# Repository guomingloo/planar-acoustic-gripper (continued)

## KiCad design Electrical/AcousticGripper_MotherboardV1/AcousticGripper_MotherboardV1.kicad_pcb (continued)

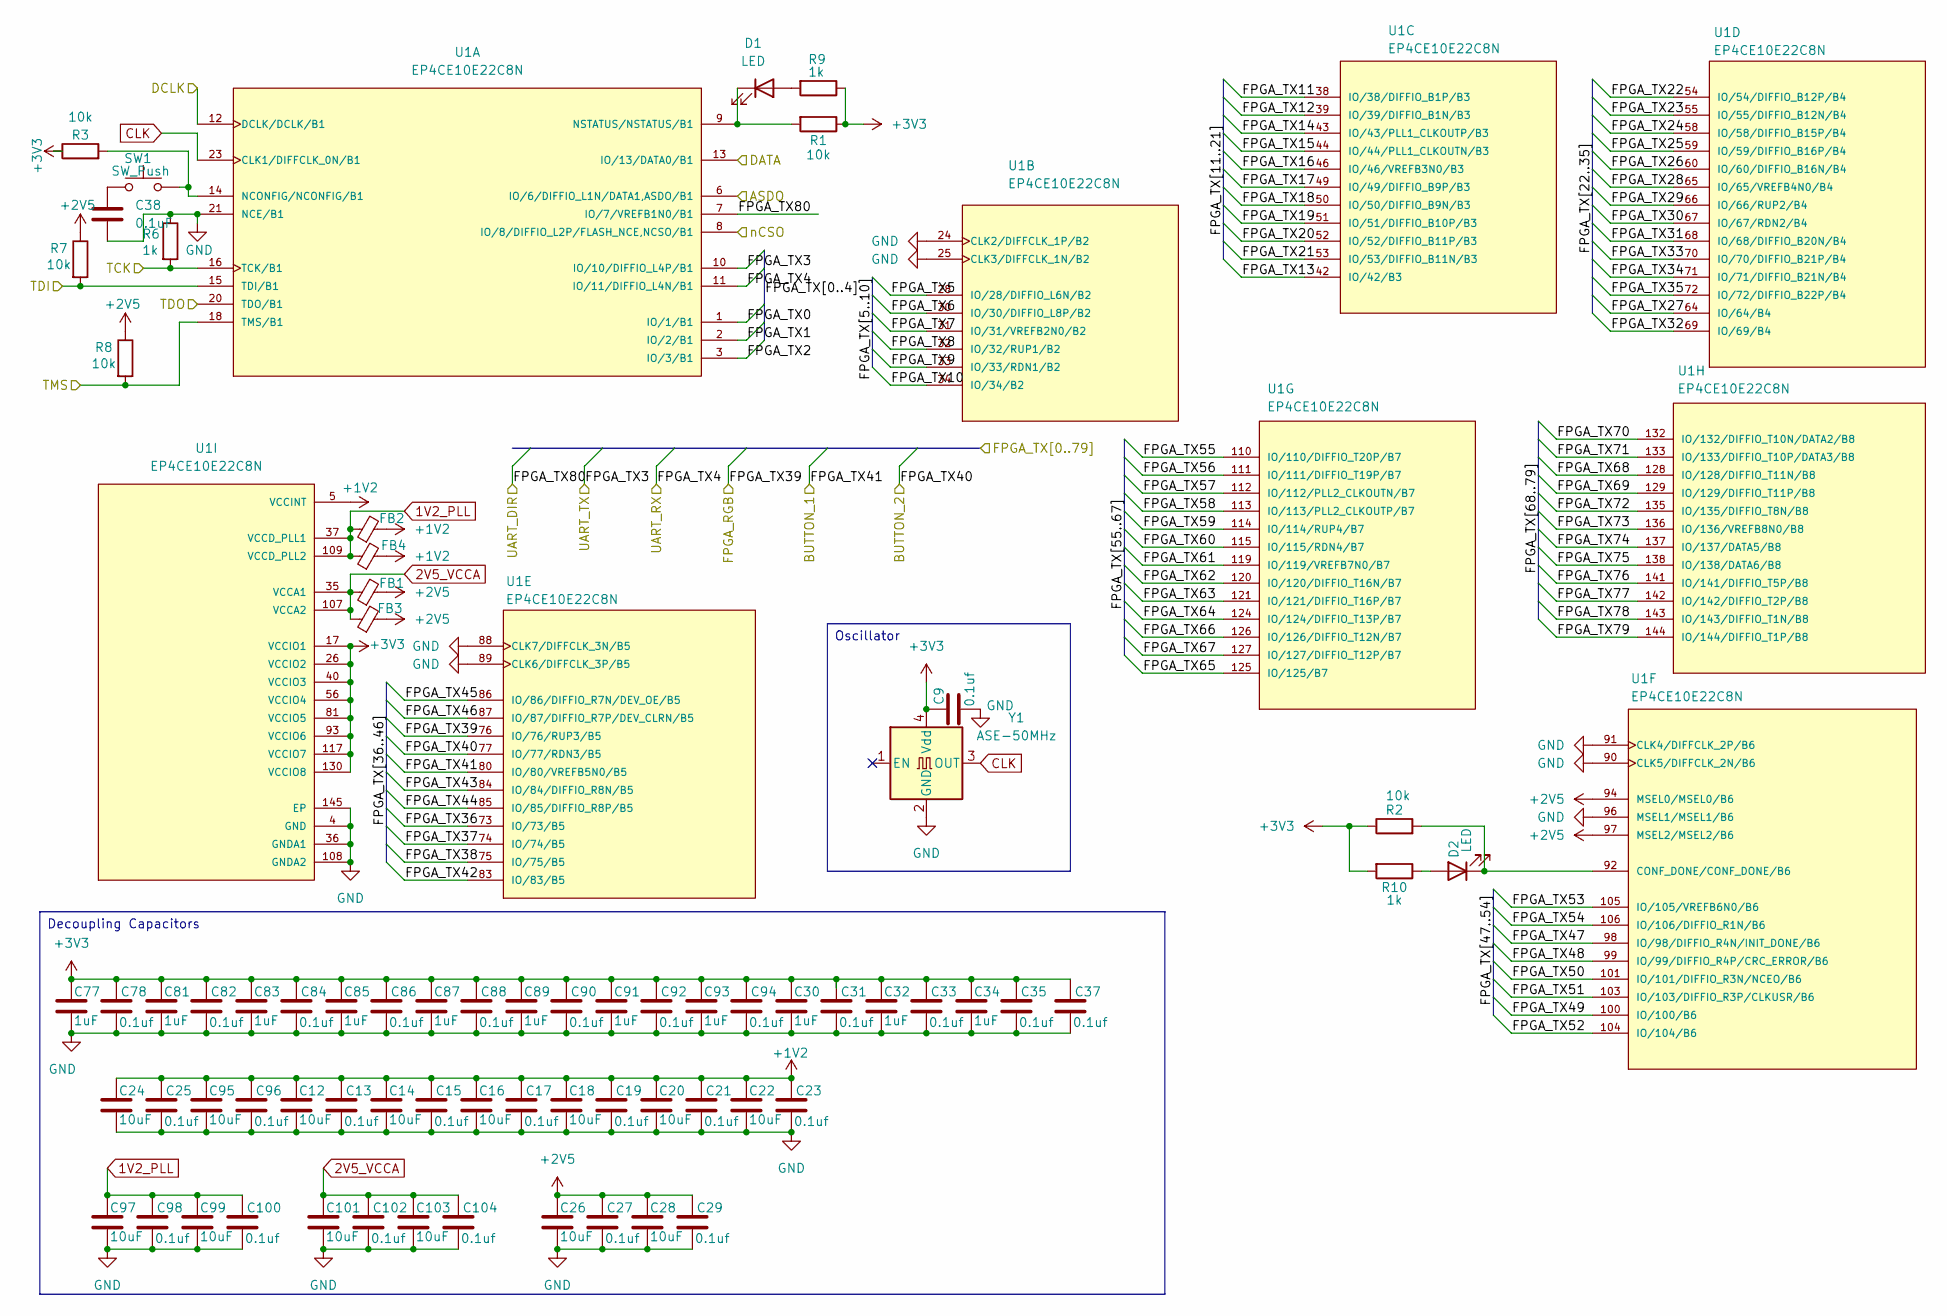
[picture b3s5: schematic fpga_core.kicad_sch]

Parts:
C9, C13, C15, C17, C19, C21, C23, C25, C27, C29, C31, C33, C35, C37, C78, C82, C84, C86, C88, C90, C92, C94, C96, C98, C100, C102, C104: 0.1uf; C_0402_1005Metric
C12, C14, C16, C18, C20, C22, C24, C26, C28, C95, C97, C99, C101, C103: 10uF; C_0402_1005Metric
C30, C32, C34, C77, C81, C83, C85, C87, C89, C91, C93: 1uF; C_0402_1005Metric
C38: 0.1uF; C_0402_1005Metric
D1, D2: LED; LED_D3.0mm
FB1, FB2, FB3, FB4: FerriteBead_Small; L_0402_1005Metric
R1, R2, R3, R7, R8: 10k; R_0402_1005Metric
R6, R9, R10: 1k; R_0402_1005Metric
SW1: SW_Push; SW_Push_SPST_NO_Alps_SKRK
U1: EP4CE10E22C8N; QFP50P2200X2200X165-145N
Y1: ASE-50MHz; Oscillator_SMD_Abracon_ASE-4Pin_3.2x2.5mm

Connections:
1V2_PLL: C97.1, C98.1, C99.1, C100.1, FB2.1, FB4.1, U1.37 (VCCD_PLL1), U1.109 (VCCD_PLL2)
2V5_VCCA: C101.1, C102.1, C103.1, C104.1, FB1.1, FB3.1, U1.35 (VCCA1), U1.107 (VCCA2)
+1V2: C12.1, C13.1, C14.1, C15.1, C16.1, C17.1, C18.1, C19.1, C20.1, C21.1, C22.1, C23.1, C24.1, C25.1, C95.1, C96.1, FB2.2, FB4.2, U1.5 (VCCINT), U1.29 (VCCINT), U1.45 (VCCINT), U1.61 (VCCINT), U1.78 (VCCINT), U1.102 (VCCINT), U1.116 (VCCINT), U1.134 (VCCINT); also elsewhere on the board
+2V5: C26.1, C27.1, C28.1, C29.1, FB1.2, FB3.2, R7.1, R8.1, U1.94 (MSEL0/MSEL0/B6), U1.97 (MSEL2/MSEL2/B6); also elsewhere on the board
+3V3: C9.1, C30.1, C31.1, C32.1, C33.1, C34.1, C35.1, C37.1, C77.1, C78.1, C81.1, C82.1, C83.1, C84.1, C85.1, C86.1, C87.1, C88.1, C89.1, C90.1, C91.1, C92.1, C93.1, C94.1, R1.1, R2.1, R3.1, R9.1, R10.2, U1.17 (VCCIO1), U1.26 (VCCIO2), U1.40 (VCCIO3), U1.47 (VCCIO3), U1.56 (VCCIO4), U1.62 (VCCIO4), U1.81 (VCCIO5), U1.93 (VCCIO6), U1.117 (VCCIO7), U1.122 (VCCIO7), U1.130 (VCCIO8), U1.139 (VCCIO8), Y1.4 (Vdd); also elsewhere on the board
/Configuration/ASDO: U1.6 (IO/6/DIFFIO_L1N/DATA1,ASDO/B1); also elsewhere on the board
/Configuration/DATA: U1.13 (IO/13/DATA0/B1); also elsewhere on the board
/Configuration/DCLK: U1.12 (DCLK/DCLK/B1); also elsewhere on the board
/Configuration/TCK: R6.2, U1.16 (TCK/B1); also elsewhere on the board
/Configuration/TDI: R7.2, U1.15 (TDI/B1); also elsewhere on the board
/Configuration/TDO: U1.20 (TDO/B1); also elsewhere on the board
/Configuration/TMS: R8.2, U1.18 (TMS/B1); also elsewhere on the board
/Configuration/nCSO: U1.8 (IO/8/DIFFIO_L2P/FLASH_NCE,NCSO/B1); also elsewhere on the board
/FPGA_Core/FPGA_TX0: U1.1 (IO/1/B1); also elsewhere on the board
/FPGA_Core/FPGA_TX1: U1.2 (IO/2/B1); also elsewhere on the board
/FPGA_Core/FPGA_TX2: U1.3 (IO/3/B1); also elsewhere on the board
/FPGA_Core/FPGA_TX3: U1.10 (IO/10/DIFFIO_L4P/B1); also elsewhere on the board
/FPGA_Core/FPGA_TX4: U1.11 (IO/11/DIFFIO_L4N/B1); also elsewhere on the board
/FPGA_Core/FPGA_TX5: U1.28 (IO/28/DIFFIO_L6N/B2); also elsewhere on the board
/FPGA_Core/FPGA_TX6: U1.30 (IO/30/DIFFIO_L8P/B2); also elsewhere on the board
/FPGA_Core/FPGA_TX7: U1.31 (IO/31/VREFB2N0/B2); also elsewhere on the board
/FPGA_Core/FPGA_TX8: U1.32 (IO/32/RUP1/B2); also elsewhere on the board
/FPGA_Core/FPGA_TX9: U1.33 (IO/33/RDN1/B2); also elsewhere on the board
/FPGA_Core/FPGA_TX10: U1.34 (IO/34/B2); also elsewhere on the board
/FPGA_Core/FPGA_TX11: U1.38 (IO/38/DIFFIO_B1P/B3); also elsewhere on the board
/FPGA_Core/FPGA_TX12: U1.39 (IO/39/DIFFIO_B1N/B3); also elsewhere on the board
/FPGA_Core/FPGA_TX13: U1.42 (IO/42/B3); also elsewhere on the board
/FPGA_Core/FPGA_TX14: U1.43 (IO/43/PLL1_CLKOUTP/B3); also elsewhere on the board
/FPGA_Core/FPGA_TX15: U1.44 (IO/44/PLL1_CLKOUTN/B3); also elsewhere on the board
/FPGA_Core/FPGA_TX16: U1.46 (IO/46/VREFB3N0/B3); also elsewhere on the board
/FPGA_Core/FPGA_TX17: U1.49 (IO/49/DIFFIO_B9P/B3); also elsewhere on the board
/FPGA_Core/FPGA_TX18: U1.50 (IO/50/DIFFIO_B9N/B3); also elsewhere on the board
/FPGA_Core/FPGA_TX19: U1.51 (IO/51/DIFFIO_B10P/B3); also elsewhere on the board
/FPGA_Core/FPGA_TX20: U1.52 (IO/52/DIFFIO_B11P/B3); also elsewhere on the board
/FPGA_Core/FPGA_TX21: U1.53 (IO/53/DIFFIO_B11N/B3); also elsewhere on the board
/FPGA_Core/FPGA_TX22: U1.54 (IO/54/DIFFIO_B12P/B4); also elsewhere on the board
/FPGA_Core/FPGA_TX23: U1.55 (IO/55/DIFFIO_B12N/B4); also elsewhere on the board
/FPGA_Core/FPGA_TX24: U1.58 (IO/58/DIFFIO_B15P/B4); also elsewhere on the board
/FPGA_Core/FPGA_TX25: U1.59 (IO/59/DIFFIO_B16P/B4); also elsewhere on the board
/FPGA_Core/FPGA_TX26: U1.60 (IO/60/DIFFIO_B16N/B4); also elsewhere on the board
/FPGA_Core/FPGA_TX27: U1.64 (IO/64/B4); also elsewhere on the board
/FPGA_Core/FPGA_TX28: U1.65 (IO/65/VREFB4N0/B4); also elsewhere on the board
/FPGA_Core/FPGA_TX29: U1.66 (IO/66/RUP2/B4); also elsewhere on the board
/FPGA_Core/FPGA_TX30: U1.67 (IO/67/RDN2/B4); also elsewhere on the board
/FPGA_Core/FPGA_TX31: U1.68 (IO/68/DIFFIO_B20N/B4); also elsewhere on the board
/FPGA_Core/FPGA_TX32: U1.69 (IO/69/B4); also elsewhere on the board
/FPGA_Core/FPGA_TX33: U1.70 (IO/70/DIFFIO_B21P/B4); also elsewhere on the board
/FPGA_Core/FPGA_TX34: U1.71 (IO/71/DIFFIO_B21N/B4); also elsewhere on the board
/FPGA_Core/FPGA_TX35: U1.72 (IO/72/DIFFIO_B22P/B4); also elsewhere on the board
/FPGA_Core/FPGA_TX36: U1.73 (IO/73/B5); also elsewhere on the board
/FPGA_Core/FPGA_TX37: U1.74 (IO/74/B5); also elsewhere on the board
/FPGA_Core/FPGA_TX38: U1.75 (IO/75/B5); also elsewhere on the board
/FPGA_Core/FPGA_TX39: U1.76 (IO/76/RUP3/B5); also elsewhere on the board
/FPGA_Core/FPGA_TX40: U1.77 (IO/77/RDN3/B5); also elsewhere on the board
/FPGA_Core/FPGA_TX41: U1.80 (IO/80/VREFB5N0/B5); also elsewhere on the board
/FPGA_Core/FPGA_TX42: U1.83 (IO/83/B5); also elsewhere on the board
/FPGA_Core/FPGA_TX43: U1.84 (IO/84/DIFFIO_R8N/B5); also elsewhere on the board
/FPGA_Core/FPGA_TX44: U1.85 (IO/85/DIFFIO_R8P/B5); also elsewhere on the board
/FPGA_Core/FPGA_TX45: U1.86 (IO/86/DIFFIO_R7N/DEV_OE/B5); also elsewhere on the board
/FPGA_Core/FPGA_TX46: U1.87 (IO/87/DIFFIO_R7P/DEV_CLRN/B5); also elsewhere on the board
/FPGA_Core/FPGA_TX47: U1.98 (IO/98/DIFFIO_R4N/INIT_DONE/B6); also elsewhere on the board
/FPGA_Core/FPGA_TX48: U1.99 (IO/99/DIFFIO_R4P/CRC_ERROR/B6); also elsewhere on the board
/FPGA_Core/FPGA_TX49: U1.100 (IO/100/B6); also elsewhere on the board
/FPGA_Core/FPGA_TX50: U1.101 (IO/101/DIFFIO_R3N/NCEO/B6); also elsewhere on the board
/FPGA_Core/FPGA_TX51: U1.103 (IO/103/DIFFIO_R3P/CLKUSR/B6); also elsewhere on the board
/FPGA_Core/FPGA_TX52: U1.104 (IO/104/B6); also elsewhere on the board
/FPGA_Core/FPGA_TX53: U1.105 (IO/105/VREFB6N0/B6); also elsewhere on the board
/FPGA_Core/FPGA_TX54: U1.106 (IO/106/DIFFIO_R1N/B6); also elsewhere on the board
/FPGA_Core/FPGA_TX55: U1.110 (IO/110/DIFFIO_T20P/B7); also elsewhere on the board
/FPGA_Core/FPGA_TX56: U1.111 (IO/111/DIFFIO_T19P/B7); also elsewhere on the board
/FPGA_Core/FPGA_TX57: U1.112 (IO/112/PLL2_CLKOUTN/B7); also elsewhere on the board
/FPGA_Core/FPGA_TX58: U1.113 (IO/113/PLL2_CLKOUTP/B7); also elsewhere on the board
/FPGA_Core/FPGA_TX59: U1.114 (IO/114/RUP4/B7); also elsewhere on the board
/FPGA_Core/FPGA_TX60: U1.115 (IO/115/RDN4/B7); also elsewhere on the board
/FPGA_Core/FPGA_TX61: U1.119 (IO/119/VREFB7N0/B7); also elsewhere on the board
/FPGA_Core/FPGA_TX62: U1.120 (IO/120/DIFFIO_T16N/B7); also elsewhere on the board
/FPGA_Core/FPGA_TX63: U1.121 (IO/121/DIFFIO_T16P/B7); also elsewhere on the board
/FPGA_Core/FPGA_TX64: U1.124 (IO/124/DIFFIO_T13P/B7); also elsewhere on the board
/FPGA_Core/FPGA_TX65: U1.125 (IO/125/B7); also elsewhere on the board
/FPGA_Core/FPGA_TX66: U1.126 (IO/126/DIFFIO_T12N/B7); also elsewhere on the board
/FPGA_Core/FPGA_TX67: U1.127 (IO/127/DIFFIO_T12P/B7); also elsewhere on the board
/FPGA_Core/FPGA_TX68: U1.128 (IO/128/DIFFIO_T11N/B8); also elsewhere on the board
/FPGA_Core/FPGA_TX69: U1.129 (IO/129/DIFFIO_T11P/B8); also elsewhere on the board
/FPGA_Core/FPGA_TX70: U1.132 (IO/132/DIFFIO_T10N/DATA2/B8); also elsewhere on the board
/FPGA_Core/FPGA_TX71: U1.133 (IO/133/DIFFIO_T10P/DATA3/B8); also elsewhere on the board
/FPGA_Core/FPGA_TX72: U1.135 (IO/135/DIFFIO_T8N/B8); also elsewhere on the board
/FPGA_Core/FPGA_TX73: U1.136 (IO/136/VREFB8N0/B8); also elsewhere on the board
/FPGA_Core/FPGA_TX74: U1.137 (IO/137/DATA5/B8); also elsewhere on the board
/FPGA_Core/FPGA_TX75: U1.138 (IO/138/DATA6/B8); also elsewhere on the board
/FPGA_Core/FPGA_TX76: U1.141 (IO/141/DIFFIO_T5P/B8); also elsewhere on the board
/FPGA_Core/FPGA_TX77: U1.142 (IO/142/DIFFIO_T2P/B8); also elsewhere on the board
/FPGA_Core/FPGA_TX78: U1.143 (IO/143/DIFFIO_T1N/B8); also elsewhere on the board
/FPGA_Core/FPGA_TX79: U1.144 (IO/144/DIFFIO_T1P/B8); also elsewhere on the board
/FPGA_Core/FPGA_TX80: U1.7 (IO/7/VREFB1N0/B1); also elsewhere on the board
CLK: U1.23 (CLK1/DIFFCLK_0N/B1), Y1.3 (OUT)
GND: C9.2, C12.2, C13.2, C14.2, C15.2, C16.2, C17.2, C18.2, C19.2, C20.2, C21.2, C22.2, C23.2, C24.2, C25.2, C26.2, C27.2, C28.2, C29.2, C30.2, C31.2, C32.2, C33.2, C34.2, C35.2, C37.2, C38.2, C77.2, C78.2, C81.2, C82.2, C83.2, C84.2, C85.2, C86.2, C87.2, C88.2, C89.2, C90.2, C91.2, C92.2, C93.2, C94.2, C95.2, C96.2, C97.2, C98.2, C99.2, C100.2, C101.2, C102.2, C103.2, C104.2, R6.1, U1.4 (GND), U1.19 (GND), U1.21 (NCE/B1), U1.22 (GND), U1.24 (CLK2/DIFFCLK_1P/B2), U1.25 (CLK3/DIFFCLK_1N/B2), U1.27 (GND), U1.36 (GNDA1), U1.41 (GND), U1.48 (GND), U1.57 (GND), U1.63 (GND), U1.79 (GND), U1.82 (GND), U1.88 (CLK7/DIFFCLK_3N/B5), U1.89 (CLK6/DIFFCLK_3P/B5), U1.90 (CLK5/DIFFCLK_2N/B6), U1.91 (CLK4/DIFFCLK_2P/B6), U1.95 (GND), U1.96 (MSEL1/MSEL1/B6), U1.108 (GNDA2), U1.118 (GND), U1.123 (GND), U1.131 (GND), U1.140 (GND), U1.145 (EP), Y1.2 (GND); also elsewhere on the board
unnamed: C38.1, SW1.1
unnamed: D1.2 (A), R9.2
unnamed: D1.1 (K), R1.2, U1.9 (NSTATUS/NSTATUS/B1)
unnamed: D2.2 (A), R10.1
unnamed: D2.1 (K), R2.2, U1.92 (CONF_DONE/CONF_DONE/B6)
unnamed: R3.2, SW1.2, U1.14 (NCONFIG/NCONFIG/B1)

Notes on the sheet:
Oscillator
Decoupling Capacitors

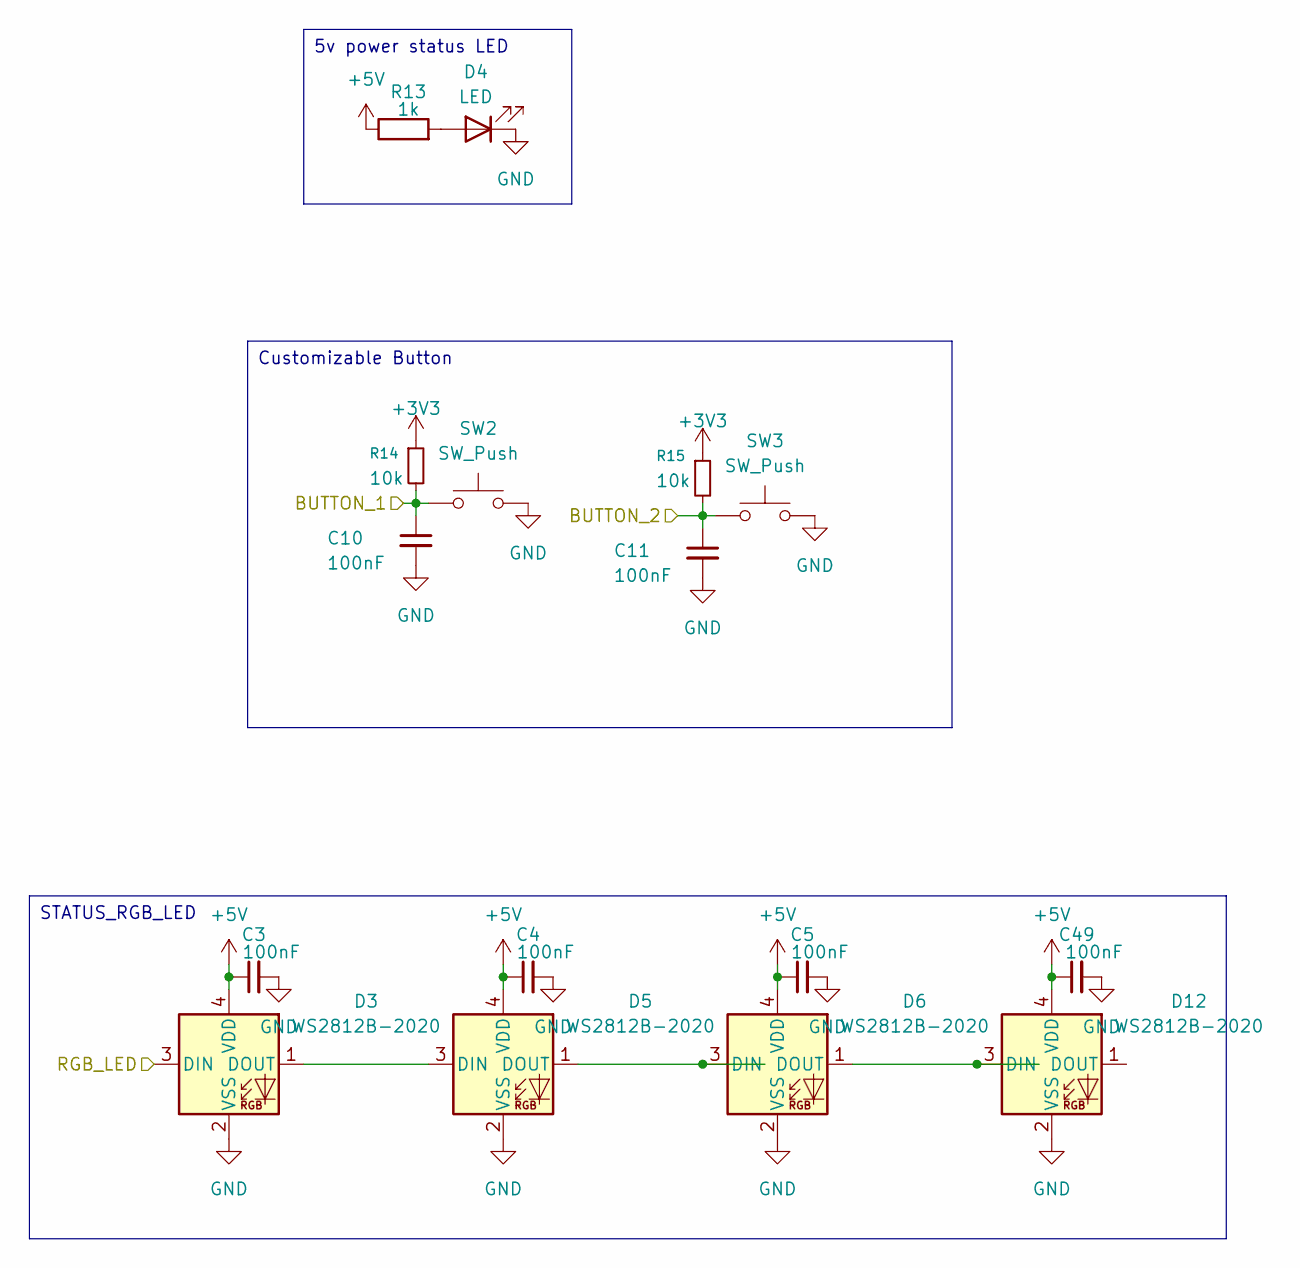
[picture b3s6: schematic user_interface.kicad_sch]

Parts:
C3, C4, C5, C10, C11, C49: 100nF; C_0402_1005Metric
D3, D5, D6, D12: WS2812B-2020; LED_WS2812B-2020_PLCC4_2.0x2.0mm
D4: LED; LED_D3.0mm
R13: 1k; R_0402_1005Metric
R14, R15: 10k; R_0402_1005Metric
SW2, SW3: SW_Push; SW_Push_SPST_NO_Alps_SKRK

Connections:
+3V3: R14.1, R15.1; also elsewhere on the board
+5V: C3.1, C4.1, C5.1, C49.1, D3.4 (VDD), D5.4 (VDD), D6.4 (VDD), D12.4 (VDD), R13.1; also elsewhere on the board
/FPGA_Core/FPGA_TX40: C11.1, R15.2, SW3.1; also elsewhere on the board
/FPGA_Core/FPGA_TX41: C10.1, R14.2, SW2.1; also elsewhere on the board
/IO_Interface/RGB_LED: D3.3 (DIN); also elsewhere on the board
GND: C3.2, C4.2, C5.2, C10.2, C11.2, C49.2, D3.2 (VSS), D4.1 (K), D5.2 (VSS), D6.2 (VSS), D12.2 (VSS), SW2.2, SW3.2; also elsewhere on the board
unnamed: D3.1 (DOUT), D5.3 (DIN)
unnamed: D4.2 (A), R13.2
unnamed: D5.1 (DOUT), D6.3 (DIN)
unnamed: D6.1 (DOUT), D12.3 (DIN)

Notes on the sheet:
Customizable Button
STATUS_RGB_LED
5v power status LED

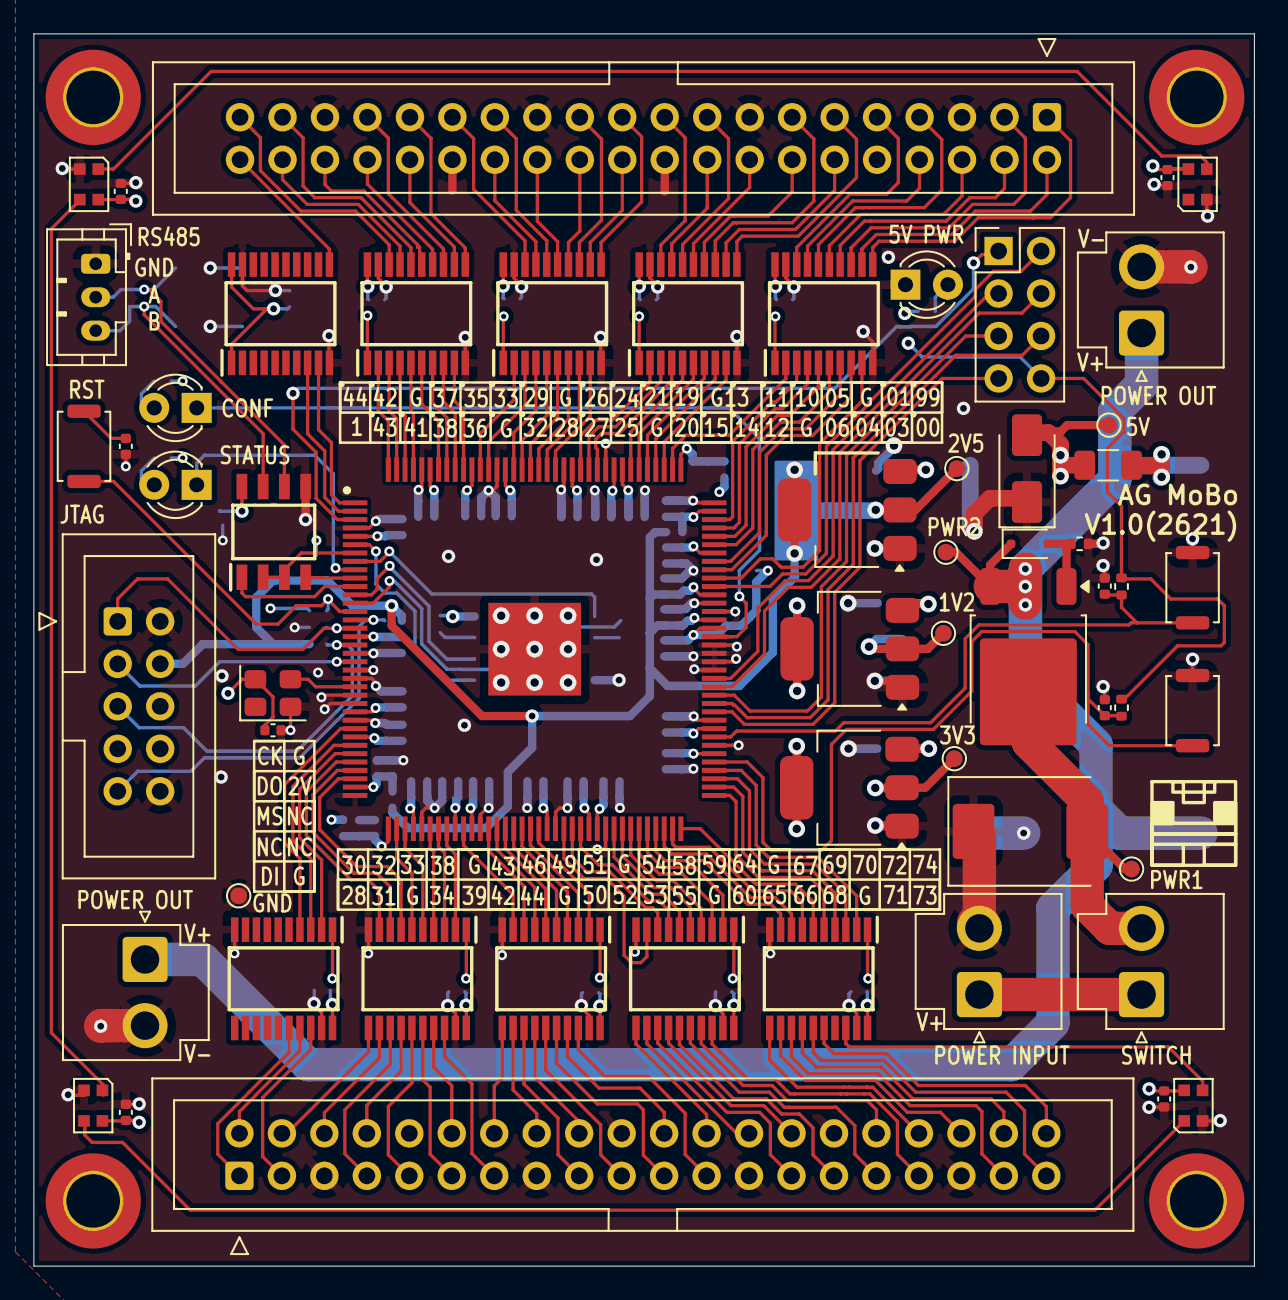
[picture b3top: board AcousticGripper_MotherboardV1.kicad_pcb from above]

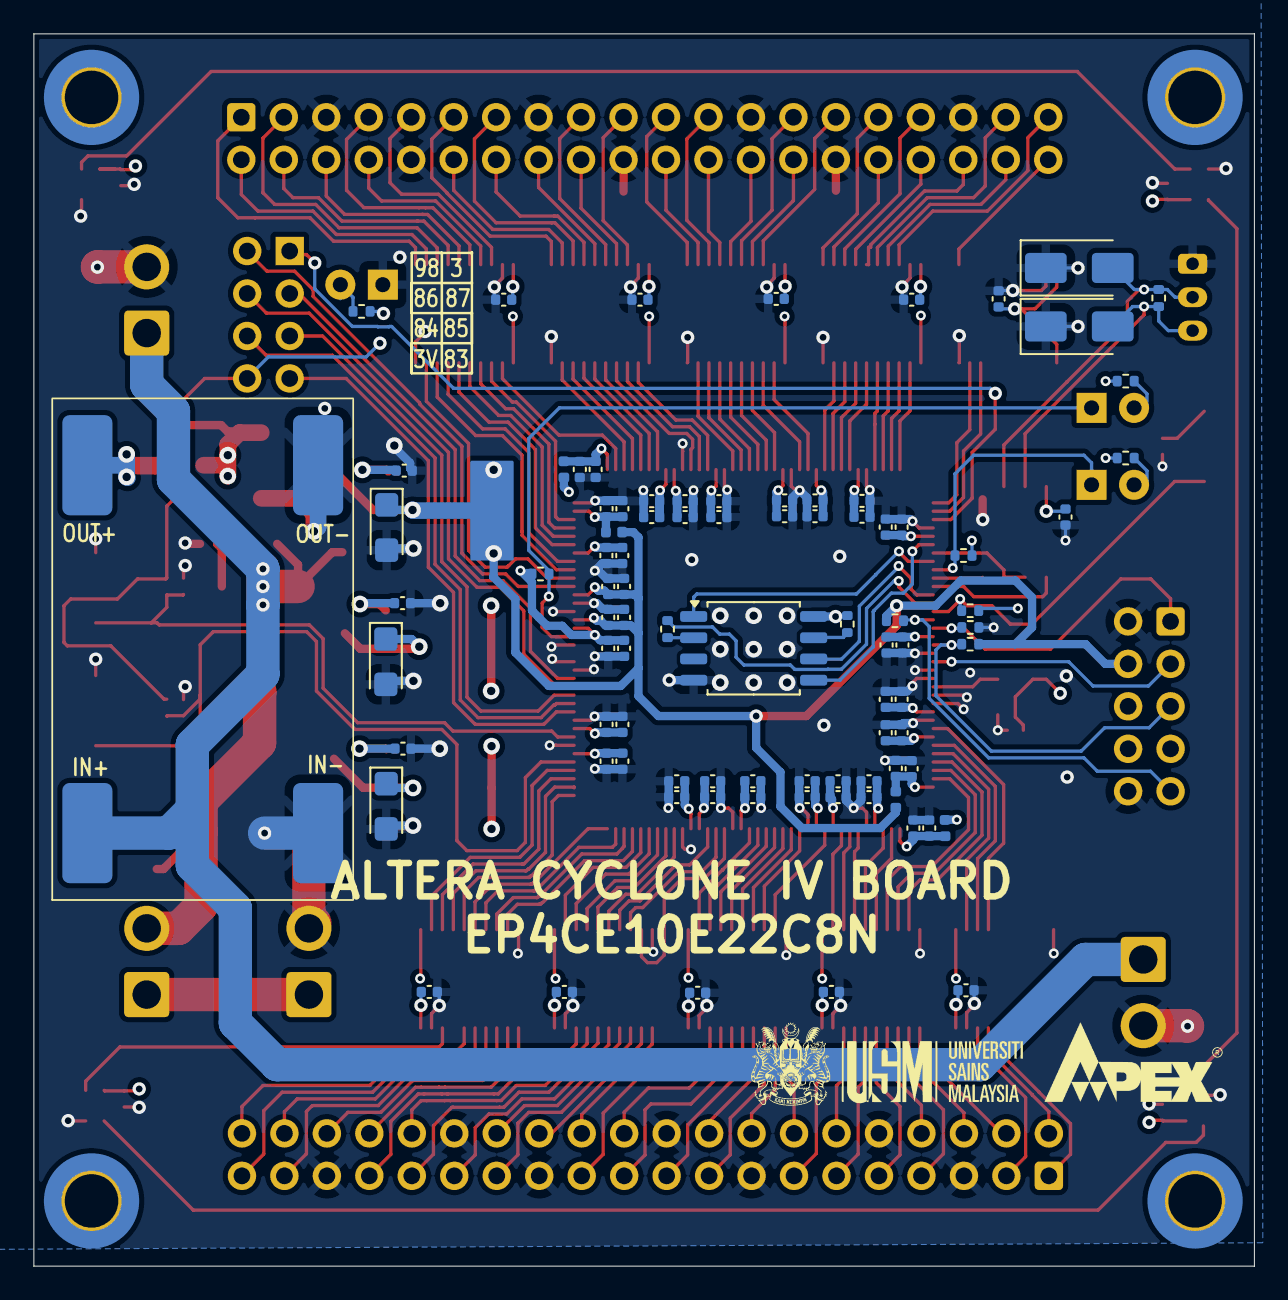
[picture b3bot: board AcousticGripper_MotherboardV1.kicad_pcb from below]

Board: 4 copper layers, 73.0 x 73.7 mm, 147 parts (89 on the bottom side), 183 nets.

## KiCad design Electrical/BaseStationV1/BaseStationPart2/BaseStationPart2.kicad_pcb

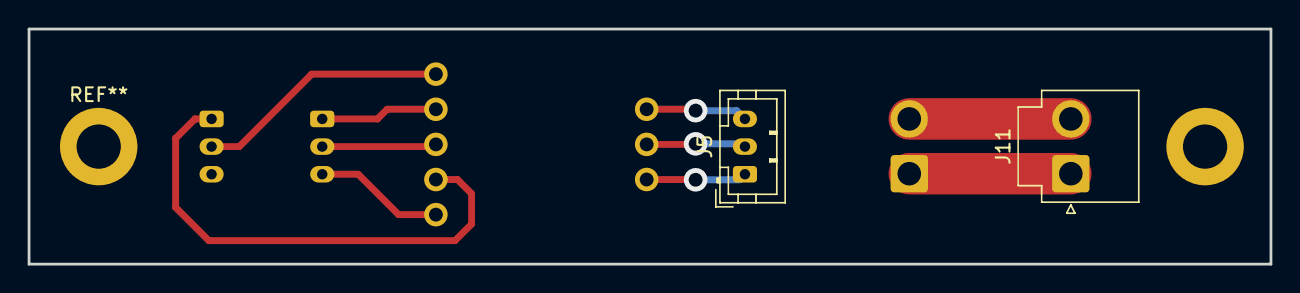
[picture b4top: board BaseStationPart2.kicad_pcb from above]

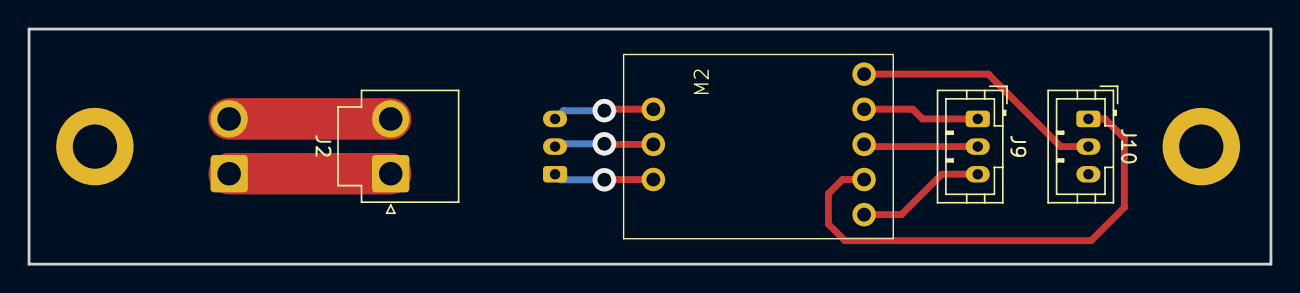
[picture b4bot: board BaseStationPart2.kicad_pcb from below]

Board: 2 copper layers, 89.8 x 17.0 mm, 6 parts (4 on the bottom side), 10 nets.

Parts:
J2, J11: Conn_01x02_Pin; JST_VH_B2P-VH-B_1x02_P3.96mm_Vertical
J5, J9, J10: Conn_01x03_Pin; JST_PH_B3B-PH-K_1x03_P2.00mm_Vertical
M2: MAX3485_Module

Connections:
+3V3: J10.1, M2.5 (VCC)
GND: J10.2, M2.8 (GND)
unnamed: J9.1, M2.7 (TX)
unnamed: J9.2, M2.6 (RX)
unnamed: J9.3, M2.4 (EN)
unnamed: J5.1, M2.1 (GND)
unnamed: J5.2, M2.2 (A)
unnamed: J5.3, M2.3 (B)
unnamed: J2.1, J11.1
unnamed: J2.2, J11.2

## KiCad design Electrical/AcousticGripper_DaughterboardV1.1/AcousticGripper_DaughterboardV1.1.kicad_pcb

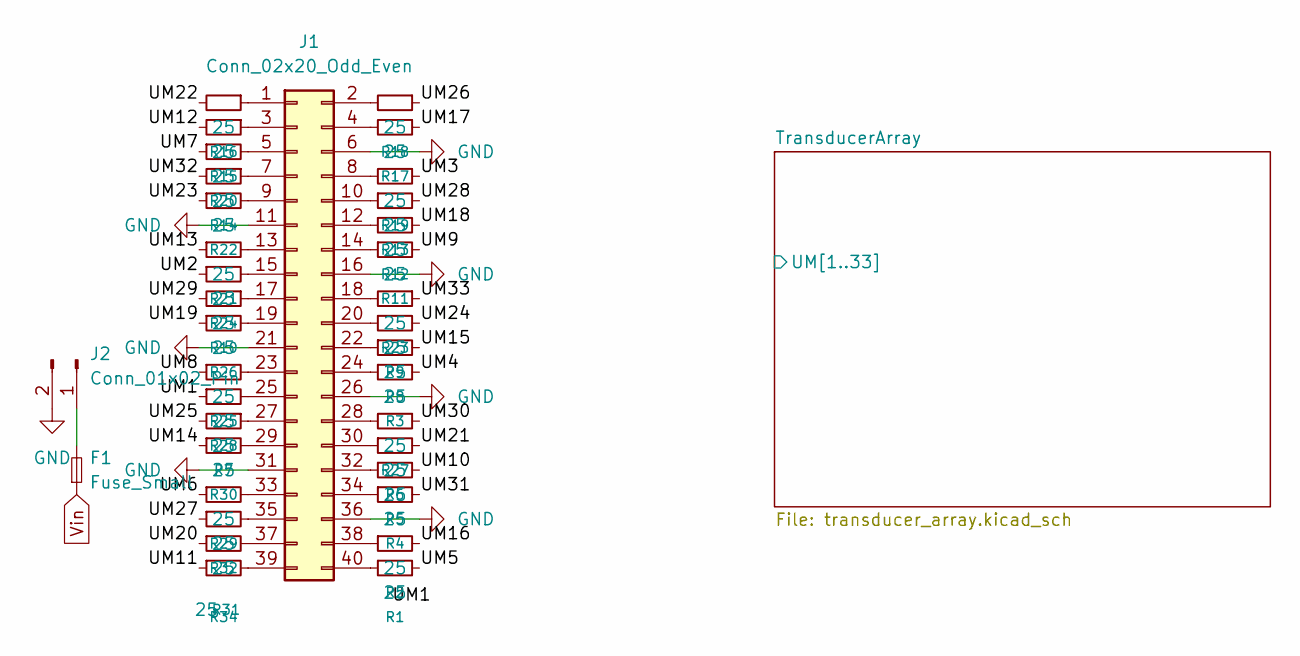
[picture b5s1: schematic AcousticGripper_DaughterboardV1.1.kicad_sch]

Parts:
F1: Fuse_Small; Fuse_Littelfuse-NANO2-451_453
J1: Conn_02x20_Odd_Even; IDC-Header_2x20_P2.54mm_Vertical
J2: Conn_01x02_Pin; JST_VH_B2P-VH-B_1x02_P3.96mm_Vertical
R1, R2, R3, R4, R5, R6, R7, R8, R9, R10, R11, R12, R13, R14, R15, R16, R17, R18, R19, R20, R21, R22, R23, R24, R25, R26, R27, R28, R29, R30, R31, R32, R34: 25; R_0402_1005Metric

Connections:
/TransducerArray/UM1: R28.1; also elsewhere on the board
/TransducerArray/UM2: R24.1; also elsewhere on the board
/TransducerArray/UM3: R19.1; also elsewhere on the board
/TransducerArray/UM4: R3.2; also elsewhere on the board
/TransducerArray/UM5: R1.2; also elsewhere on the board
/TransducerArray/UM6: R29.1; also elsewhere on the board
/TransducerArray/UM7: R20.1; also elsewhere on the board
/TransducerArray/UM8: R25.1; also elsewhere on the board
/TransducerArray/UM9: R11.2; also elsewhere on the board
/TransducerArray/UM10: R5.2; also elsewhere on the board
/TransducerArray/UM11: R34.1; also elsewhere on the board
/TransducerArray/UM12: R15.2; also elsewhere on the board
/TransducerArray/UM13: R21.1; also elsewhere on the board
/TransducerArray/UM14: R30.1; also elsewhere on the board
/TransducerArray/UM15: R8.2; also elsewhere on the board
/TransducerArray/UM16: R2.2; also elsewhere on the board
/TransducerArray/UM17: R17.1; also elsewhere on the board
/TransducerArray/UM18: R12.2; also elsewhere on the board
/TransducerArray/UM19: R26.1; also elsewhere on the board
/TransducerArray/UM20: R31.1; also elsewhere on the board
/TransducerArray/UM21: R6.2; also elsewhere on the board
/TransducerArray/UM22: R16.2; also elsewhere on the board
/TransducerArray/UM23: R22.1; also elsewhere on the board
/TransducerArray/UM24: R9.2; also elsewhere on the board
/TransducerArray/UM25: R7.2; also elsewhere on the board
/TransducerArray/UM26: R18.1; also elsewhere on the board
/TransducerArray/UM27: R32.1; also elsewhere on the board
/TransducerArray/UM28: R13.2; also elsewhere on the board
/TransducerArray/UM29: R10.2; also elsewhere on the board
/TransducerArray/UM30: R27.1; also elsewhere on the board
/TransducerArray/UM31: R4.2; also elsewhere on the board
/TransducerArray/UM32: R14.2; also elsewhere on the board
/TransducerArray/UM33: R23.1; also elsewhere on the board
GND: J1.6, J1.11, J1.16, J1.21, J1.26, J1.31, J1.36, J2.2; also elsewhere on the board
unnamed: J1.1, R16.1
unnamed: J1.2, R18.2
unnamed: J1.3, R15.1
unnamed: J1.4, R17.2
unnamed: J1.5, R20.2
unnamed: J1.7, R14.1
unnamed: J1.8, R19.2
unnamed: J1.9, R22.2
unnamed: J1.10, R13.1
unnamed: J1.12, R12.1
unnamed: J1.13, R21.2
unnamed: J1.14, R11.1
unnamed: J1.15, R24.2
unnamed: J1.17, R10.1
unnamed: J1.18, R23.2
unnamed: J1.19, R26.2
unnamed: J1.20, R9.1
unnamed: J1.22, R8.1
unnamed: J1.23, R25.2
unnamed: J1.24, R3.1
unnamed: J1.25, R28.2
unnamed: J1.27, R7.1
unnamed: J1.28, R27.2
unnamed: J1.29, R30.2
unnamed: J1.30, R6.1
unnamed: J1.32, R5.1
unnamed: J1.33, R29.2
unnamed: J1.34, R4.1
unnamed: J1.35, R32.2
unnamed: J1.37, R31.2
unnamed: J1.38, R2.1
unnamed: J1.39, R34.2
unnamed: J1.40, R1.1
unnamed: F1.2, J2.1
Vin: F1.1; also elsewhere on the board

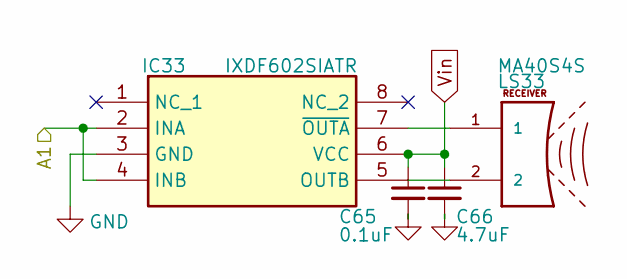
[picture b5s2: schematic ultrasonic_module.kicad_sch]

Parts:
C65: 0.1uF; C_0603_1608Metric_Pad1.08x0.95mm_HandSolder
C66: 4.7uF; C_0805_2012Metric_Pad1.18x1.45mm_HandSolder
IC33: IXDF602SIATR; IX4340N; Mouser Part Number 849-IXDF602SIATR
LS33: MA40S4S; XDCR_MA40S4S

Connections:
/TransducerArray/UM1: IC33.2 (INA), IC33.4 (INB); also elsewhere on the board
GND: C65.2, C66.2, IC33.3 (GND); also elsewhere on the board
unnamed: IC33.5 (OUTB), LS33.2
unnamed: IC33.7 (~OUTA), LS33.1
Vin: C65.1, C66.1, IC33.6 (VCC); also elsewhere on the board

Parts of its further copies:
C1, C3, C5, C7, C9, C11, C13, C15, C17, C19, C21, C23, C25, C27, C29, C31, C33, C35, C37, C39, C41, C43, C45, C47, C49, C51, C53, C55, C57, C59, C61, C63: 0.1uF; C_0603_1608Metric_Pad1.08x0.95mm_HandSolder
C2, C4, C6, C8, C10, C12, C14, C16, C18, C20, C22, C24, C26, C28, C30, C32, C34, C36, C38, C40, C42, C44, C46, C48, C50, C52, C54, C56, C58, C60, C62, C64: 4.7uF; C_0805_2012Metric_Pad1.18x1.45mm_HandSolder
IC1, IC2, IC3, IC4, IC5, IC6, IC7, IC8, IC9, IC10, IC11, IC12, IC13, IC14, IC15, IC16, IC17, IC18, IC19, IC20, IC21, IC22, IC23, IC24, IC25, IC26, IC27, IC28, IC29, IC30, IC31, IC32: IXDF602SIATR; IX4340N; Mouser Part Number 849-IXDF602SIATR
LS1, LS2, LS3, LS4, LS5, LS6, LS7, LS8, LS9, LS10, LS11, LS12, LS13, LS14, LS15, LS16, LS17, LS18, LS19, LS20, LS21, LS22, LS23, LS24, LS25, LS26, LS27, LS28, LS29, LS30, LS31, LS32: MA40S4S; XDCR_MA40S4S

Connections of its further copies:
/TransducerArray/UM2: IC2.2 (INA), IC2.4 (INB); also elsewhere on the board
/TransducerArray/UM3: IC1.2 (INA), IC1.4 (INB); also elsewhere on the board
/TransducerArray/UM4: IC3.2 (INA), IC3.4 (INB); also elsewhere on the board
/TransducerArray/UM5: IC5.2 (INA), IC5.4 (INB); also elsewhere on the board
/TransducerArray/UM6: IC4.2 (INA), IC4.4 (INB); also elsewhere on the board
/TransducerArray/UM7: IC6.2 (INA), IC6.4 (INB); also elsewhere on the board
/TransducerArray/UM8: IC8.2 (INA), IC8.4 (INB); also elsewhere on the board
/TransducerArray/UM9: IC7.2 (INA), IC7.4 (INB); also elsewhere on the board
/TransducerArray/UM10: IC9.2 (INA), IC9.4 (INB); also elsewhere on the board
/TransducerArray/UM11: IC10.2 (INA), IC10.4 (INB); also elsewhere on the board
/TransducerArray/UM12: IC11.2 (INA), IC11.4 (INB); also elsewhere on the board
/TransducerArray/UM13: IC12.2 (INA), IC12.4 (INB); also elsewhere on the board
/TransducerArray/UM14: IC14.2 (INA), IC14.4 (INB); also elsewhere on the board
/TransducerArray/UM15: IC13.2 (INA), IC13.4 (INB); also elsewhere on the board
/TransducerArray/UM16: IC15.2 (INA), IC15.4 (INB); also elsewhere on the board
/TransducerArray/UM17: IC16.2 (INA), IC16.4 (INB); also elsewhere on the board
/TransducerArray/UM18: IC17.2 (INA), IC17.4 (INB); also elsewhere on the board
/TransducerArray/UM19: IC18.2 (INA), IC18.4 (INB); also elsewhere on the board
/TransducerArray/UM20: IC20.2 (INA), IC20.4 (INB); also elsewhere on the board
/TransducerArray/UM21: IC19.2 (INA), IC19.4 (INB); also elsewhere on the board
/TransducerArray/UM22: IC21.2 (INA), IC21.4 (INB); also elsewhere on the board
/TransducerArray/UM23: IC22.2 (INA), IC22.4 (INB); also elsewhere on the board
/TransducerArray/UM24: IC23.2 (INA), IC23.4 (INB); also elsewhere on the board
/TransducerArray/UM25: IC24.2 (INA), IC24.4 (INB); also elsewhere on the board
/TransducerArray/UM26: IC26.2 (INA), IC26.4 (INB); also elsewhere on the board
/TransducerArray/UM27: IC25.2 (INA), IC25.4 (INB); also elsewhere on the board
/TransducerArray/UM28: IC27.2 (INA), IC27.4 (INB); also elsewhere on the board
/TransducerArray/UM29: IC28.2 (INA), IC28.4 (INB); also elsewhere on the board
/TransducerArray/UM30: IC29.2 (INA), IC29.4 (INB); also elsewhere on the board
/TransducerArray/UM31: IC30.2 (INA), IC30.4 (INB); also elsewhere on the board
/TransducerArray/UM32: IC31.2 (INA), IC31.4 (INB); also elsewhere on the board
/TransducerArray/UM33: IC32.2 (INA), IC32.4 (INB); also elsewhere on the board
GND: C1.2, C2.2, C3.2, C4.2, C5.2, C6.2, C7.2, C8.2, C9.2, C10.2, C11.2, C12.2, C13.2, C14.2, C15.2, C16.2, C17.2, C18.2, C19.2, C20.2, C21.2, C22.2, C23.2, C24.2, C25.2, C26.2, C27.2, C28.2, C29.2, C30.2, C31.2, C32.2, C33.2, C34.2, C35.2, C36.2, C37.2, C38.2, C39.2, C40.2, C41.2, C42.2, C43.2, C44.2, C45.2, C46.2, C47.2, C48.2, C49.2, C50.2, C51.2, C52.2, C53.2, C54.2, C55.2, C56.2, C57.2, C58.2, C59.2, C60.2, C61.2, C62.2, C63.2, C64.2, IC1.3 (GND), IC2.3 (GND), IC3.3 (GND), IC4.3 (GND), IC5.3 (GND), IC6.3 (GND), IC7.3 (GND), IC8.3 (GND), IC9.3 (GND), IC10.3 (GND), IC11.3 (GND), IC12.3 (GND), IC13.3 (GND), IC14.3 (GND), IC15.3 (GND), IC16.3 (GND), IC17.3 (GND), IC18.3 (GND), IC19.3 (GND), IC20.3 (GND), IC21.3 (GND), IC22.3 (GND), IC23.3 (GND), IC24.3 (GND), IC25.3 (GND), IC26.3 (GND), IC27.3 (GND), IC28.3 (GND), IC29.3 (GND), IC30.3 (GND), IC31.3 (GND), IC32.3 (GND); also elsewhere on the board
unnamed: IC1.5 (OUTB), LS1.2
unnamed: IC1.7 (~OUTA), LS1.1
unnamed: IC2.5 (OUTB), LS2.2
unnamed: IC2.7 (~OUTA), LS2.1
unnamed: IC3.5 (OUTB), LS3.2
unnamed: IC3.7 (~OUTA), LS3.1
unnamed: IC4.5 (OUTB), LS4.2
unnamed: IC4.7 (~OUTA), LS4.1
unnamed: IC5.5 (OUTB), LS5.2
unnamed: IC5.7 (~OUTA), LS5.1
unnamed: IC6.5 (OUTB), LS6.2
unnamed: IC6.7 (~OUTA), LS6.1
unnamed: IC7.5 (OUTB), LS7.2
unnamed: IC7.7 (~OUTA), LS7.1
unnamed: IC8.5 (OUTB), LS8.2
unnamed: IC8.7 (~OUTA), LS8.1
unnamed: IC9.5 (OUTB), LS9.2
unnamed: IC9.7 (~OUTA), LS9.1
unnamed: IC10.5 (OUTB), LS10.2
unnamed: IC10.7 (~OUTA), LS10.1
unnamed: IC11.5 (OUTB), LS11.2
unnamed: IC11.7 (~OUTA), LS11.1
unnamed: IC12.5 (OUTB), LS12.2
unnamed: IC12.7 (~OUTA), LS12.1
unnamed: IC13.5 (OUTB), LS13.2
unnamed: IC13.7 (~OUTA), LS13.1
unnamed: IC14.5 (OUTB), LS14.2
unnamed: IC14.7 (~OUTA), LS14.1
unnamed: IC15.5 (OUTB), LS15.2
unnamed: IC15.7 (~OUTA), LS15.1
unnamed: IC16.5 (OUTB), LS16.2
unnamed: IC16.7 (~OUTA), LS16.1
unnamed: IC17.5 (OUTB), LS17.2
unnamed: IC17.7 (~OUTA), LS17.1
unnamed: IC18.5 (OUTB), LS18.2
unnamed: IC18.7 (~OUTA), LS18.1
unnamed: IC19.5 (OUTB), LS19.2
unnamed: IC19.7 (~OUTA), LS19.1
unnamed: IC20.5 (OUTB), LS20.2
unnamed: IC20.7 (~OUTA), LS20.1
unnamed: IC21.5 (OUTB), LS21.2
unnamed: IC21.7 (~OUTA), LS21.1
unnamed: IC22.5 (OUTB), LS22.2
unnamed: IC22.7 (~OUTA), LS22.1
unnamed: IC23.5 (OUTB), LS23.2
unnamed: IC23.7 (~OUTA), LS23.1
unnamed: IC24.5 (OUTB), LS24.2
unnamed: IC24.7 (~OUTA), LS24.1
unnamed: IC25.5 (OUTB), LS25.2
unnamed: IC25.7 (~OUTA), LS25.1
unnamed: IC26.5 (OUTB), LS26.2
unnamed: IC26.7 (~OUTA), LS26.1
unnamed: IC27.5 (OUTB), LS27.2
unnamed: IC27.7 (~OUTA), LS27.1
unnamed: IC28.5 (OUTB), LS28.2
unnamed: IC28.7 (~OUTA), LS28.1
unnamed: IC29.5 (OUTB), LS29.2
unnamed: IC29.7 (~OUTA), LS29.1
unnamed: IC30.5 (OUTB), LS30.2
unnamed: IC30.7 (~OUTA), LS30.1
unnamed: IC31.5 (OUTB), LS31.2
unnamed: IC31.7 (~OUTA), LS31.1
unnamed: IC32.5 (OUTB), LS32.2
unnamed: IC32.7 (~OUTA), LS32.1
Vin: C1.1, C2.1, C3.1, C4.1, C5.1, C6.1, C7.1, C8.1, C9.1, C10.1, C11.1, C12.1, C13.1, C14.1, C15.1, C16.1, C17.1, C18.1, C19.1, C20.1, C21.1, C22.1, C23.1, C24.1, C25.1, C26.1, C27.1, C28.1, C29.1, C30.1, C31.1, C32.1, C33.1, C34.1, C35.1, C36.1, C37.1, C38.1, C39.1, C40.1, C41.1, C42.1, C43.1, C44.1, C45.1, C46.1, C47.1, C48.1, C49.1, C50.1, C51.1, C52.1, C53.1, C54.1, C55.1, C56.1, C57.1, C58.1, C59.1, C60.1, C61.1, C62.1, C63.1, C64.1, IC1.6 (VCC), IC2.6 (VCC), IC3.6 (VCC), IC4.6 (VCC), IC5.6 (VCC), IC6.6 (VCC), IC7.6 (VCC), IC8.6 (VCC), IC9.6 (VCC), IC10.6 (VCC), IC11.6 (VCC), IC12.6 (VCC), IC13.6 (VCC), IC14.6 (VCC), IC15.6 (VCC), IC16.6 (VCC), IC17.6 (VCC), IC18.6 (VCC), IC19.6 (VCC), IC20.6 (VCC), IC21.6 (VCC), IC22.6 (VCC), IC23.6 (VCC), IC24.6 (VCC), IC25.6 (VCC), IC26.6 (VCC), IC27.6 (VCC), IC28.6 (VCC), IC29.6 (VCC), IC30.6 (VCC), IC31.6 (VCC), IC32.6 (VCC); also elsewhere on the board
